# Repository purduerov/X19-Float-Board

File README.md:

# X19 Float Board

The Float Board manages buoyancy systems, motor drivers, sensor telemetry, and power distribution for the Purdue ROV X19 vehicle.

---

## 🚀 Quickstart: Opening the Project (Recommended)

**Always open the project using the 1-click launcher:**

* **Windows:** Double-click `LAUNCH_KICAD.bat`
* **macOS / Linux:** Run `./LAUNCH_KICAD.sh`

### What the Launcher Does Automatically:
1. ⚙️ **Configures Git Hooks & Clean Filters:** Sets up Git to strip volatile viewport/zoom coordinates on every commit, preventing merge conflicts.
2. 🔄 **Auto-Updates Component Library:** Pulls the freshest symbols, footprints, and 3D models from `purdue-rov-kicad-lib` before opening.
3. 📐 **Opens KiCad:** Launches `X19-Float-Board.kicad_pro` with all 6 central library categories pre-linked.

---

## Cloning the Repository
Clone recursively to ensure the central component library is initialized:
```bash
git clone --recursive https://github.com/purduerov/X19-Float-Board.git
cd X19-Float-Board
```

## Central Component Library & Manager GUI

The project links to the central `purdue-rov-kicad-lib` submodule mapped across 6 categories in `sym-lib-table` and `fp-lib-table`:
- `rov_passives`: Resistors, capacitors, inductors, crystals
- `rov_power`: Voltage regulators, buck/boost converters, MOSFETs, diodes
- `rov_logic`: MCUs, logic ICs, op-amps, drivers, level shifters
- `rov_connectors`: Power terminals, XT60, headers, USB, JST connectors
- `rov_sensors`: IMUs, temperature, pressure sensors
- `rov_mech`: Mounting holes, standoffs, test points

### Launching the Library Manager GUI
To browse parts, inspect footprints, edit properties, or add/delete components in the shared library:
- **Windows:** Double-click `libs\purdue-rov-kicad-lib\LIBRARY_MANAGER.bat`
- **macOS / Linux:** Run `./libs/purdue-rov-kicad-lib/LIBRARY_MANAGER.sh`

## Schematic Hierarchy

The schematic is organized across functional sub-sheets:
- `X19-Float-Board.kicad_sch`: Root top-level sheet.
- `pwr.kicad_sch`: Power regulation and distribution.
- `stm32.kicad_sch`: Main microcontroller circuit and programming interface.
- `Motor.kicad_sch`: Motor driver stages and control signals.
- `sensor.kicad_sch`: Environmental and diagnostic sensor telemetry.
- `rf.kicad_sch`: Wireless/radio transceiver circuitry.
- `switch.kicad_sch`: Power switching logic.

## Design Rules & Clearances

- High-voltage / high-current motor traces maintain isolation rules configured in `custom_rules.kicad_dru`.
- All symbols must adhere to central library guidelines.

## Automated CI/CD & DevOps Preflight Checks

All CI/CD automation and tooling are centralized in [`purduerov/pcb-devops`](https://github.com/purduerov/pcb-devops):
1. **Automated Git Clean Filters:** Configured automatically by `.githooks/pre-commit` to prevent viewport/zoom merge noise.
2. **KiCad Symbol Linting:** Validates mandatory fields (`MPN`, `Manufacturer`, `Category`, `DigiKey`, `Datasheet`, `Temp_Range`) on all library components.
3. **ERC & DRC Validation:** Executes Electrical and Design Rules Checks via KiBot in GitHub Actions.
4. **Artifact Generation:** Automatically exports Schematic PDFs, Board Layout PDFs, and Interactive HTML BOMs on every pull request.

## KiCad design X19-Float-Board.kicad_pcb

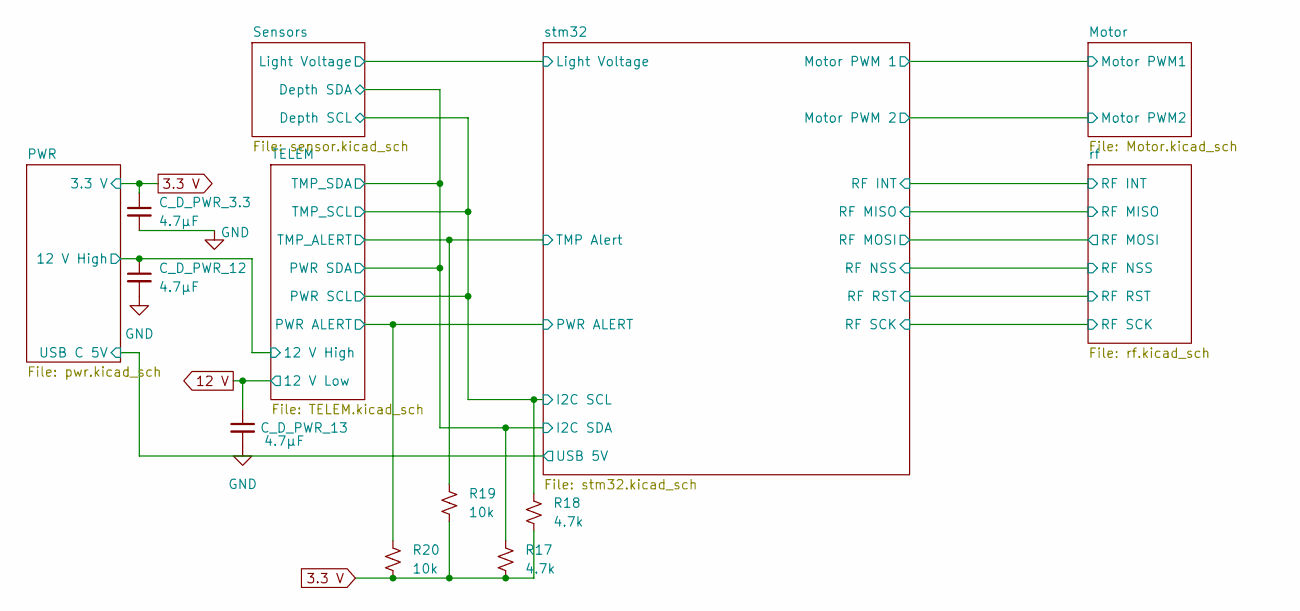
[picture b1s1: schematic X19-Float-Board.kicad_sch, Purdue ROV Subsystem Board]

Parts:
C_D_PWR_3.3, C_D_PWR_12, C_D_PWR_13: 4.7µF; C_0603_1608Metric
R17, R18: 4.7k; R_0603_1608Metric_Pad0.98x0.95mm_HandSolder
R19, R20: 10k; R_0603_1608Metric_Pad0.98x0.95mm_HandSolder

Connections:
3.3 V: C_D_PWR_3.3.1, R17.2, R18.2, R19.2, R20.2; also elsewhere on the board
12 V: C_D_PWR_13.1; also elsewhere on the board
/PWR/12 V High: C_D_PWR_12.1; also elsewhere on the board
/Sensors/Depth SCL: R18.1; also elsewhere on the board
/Sensors/Depth SDA: R17.1; also elsewhere on the board
/TELEM/PWR ALERT: R20.1; also elsewhere on the board
/TELEM/TMP_ALERT: R19.1; also elsewhere on the board
GND: C_D_PWR_3.3.2, C_D_PWR_12.2, C_D_PWR_13.2; also elsewhere on the board

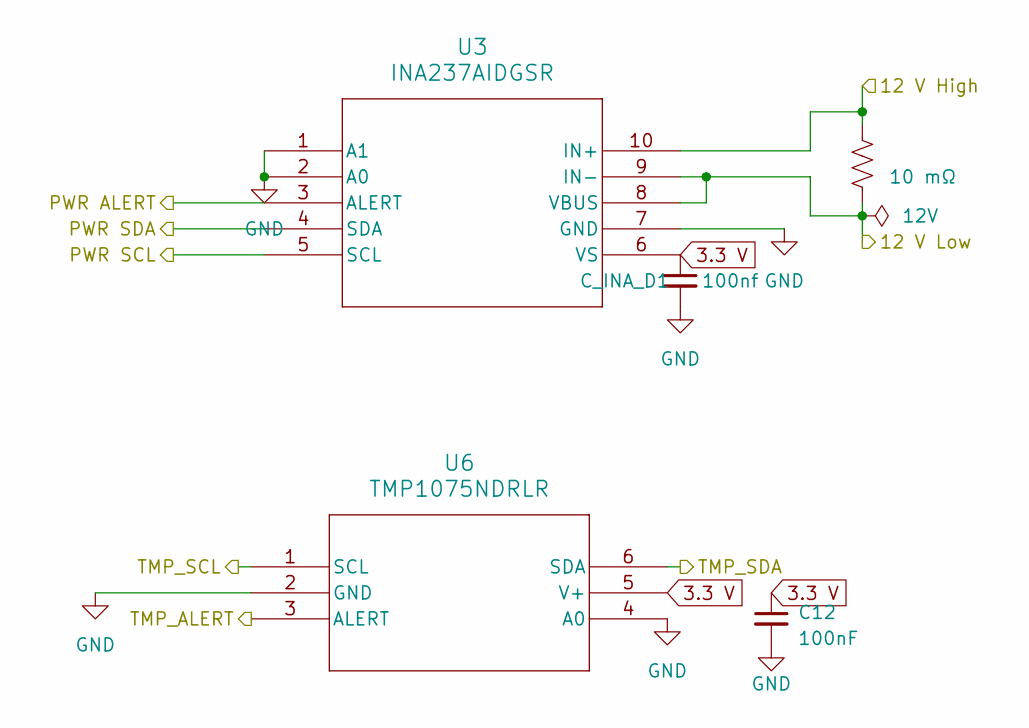
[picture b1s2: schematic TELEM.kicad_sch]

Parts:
C12: 100nF; C_0603_1608Metric_Pad1.08x0.95mm_HandSolder
C_INA_D1: 100nf; C_0603_1608Metric_Pad1.08x0.95mm_HandSolder
R1: 10 mΩ; R_2512_6332Metric_Pad1.40x3.35mm_HandSolder
U3: INA237AIDGSR; VSSOP_IDGSR_TEX; MPN INA237AIDGSR; DigiKey 296-INA237AIDGSRCT-ND
U6: TMP1075NDRLR; SOT5X3-6_DRL_TEX

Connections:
3.3 V: C12.1, C_INA_D1.1, U3.6 (VS), U6.5 (V+); also elsewhere on the board
12 V: R1.2, U3.8 (VBUS), U3.9 (IN-); also elsewhere on the board
/PWR/12 V High: R1.1, U3.10 (IN+); also elsewhere on the board
/Sensors/Depth SCL: U3.5 (SCL), U6.1 (SCL); also elsewhere on the board
/Sensors/Depth SDA: U3.4 (SDA), U6.6 (SDA); also elsewhere on the board
/TELEM/PWR ALERT: U3.3 (ALERT); also elsewhere on the board
/TELEM/TMP_ALERT: U6.3 (ALERT); also elsewhere on the board
GND: C12.2, C_INA_D1.2, U3.1 (A1), U3.2 (A0), U3.7 (GND), U6.2 (GND), U6.4 (A0); also elsewhere on the board

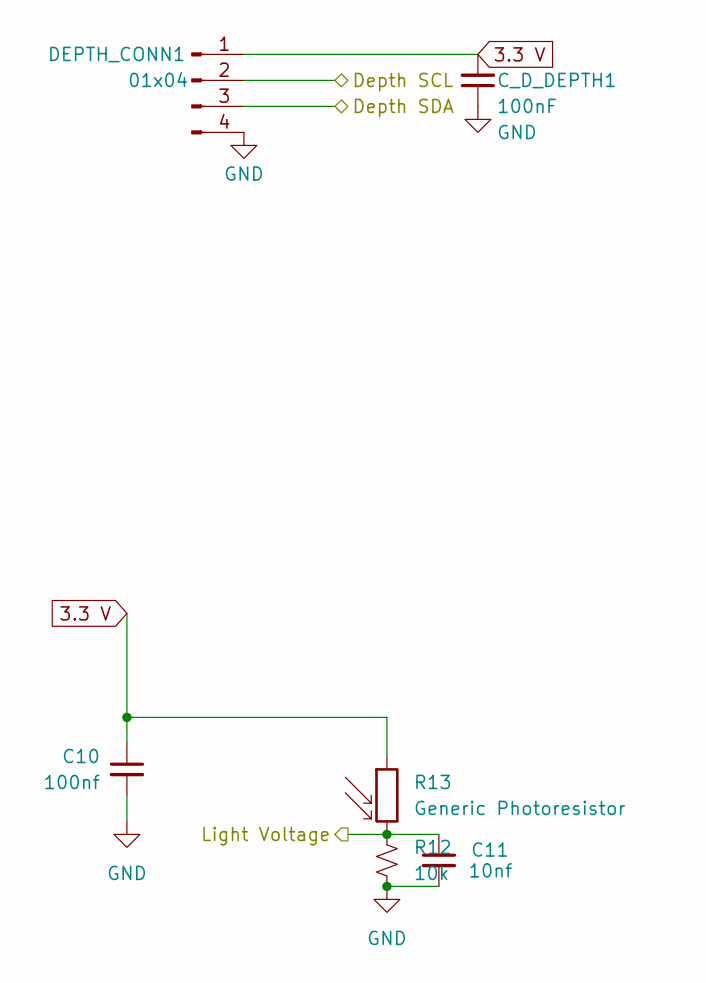
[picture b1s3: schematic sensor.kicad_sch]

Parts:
C10: 100nf; C_0603_1608Metric_Pad1.08x0.95mm_HandSolder
C11: 10nf; C_0603_1608Metric_Pad1.08x0.95mm_HandSolder
C_D_DEPTH1: 100nF; C_0603_1608Metric
DEPTH_CONN1: 01x04; Hirose_DF13-04P-1.25DS_1x04_P1.25mm_Horizontal
R12: 10k; R_0603_1608Metric_Pad0.98x0.95mm_HandSolder
R13: Generic Photoresistor; R_1206_3216Metric_Pad1.30x1.75mm_HandSolder

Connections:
3.3 V: C10.1, C_D_DEPTH1.2, DEPTH_CONN1.1, R13.1; also elsewhere on the board
/Sensors/Depth SCL: DEPTH_CONN1.2; also elsewhere on the board
/Sensors/Depth SDA: DEPTH_CONN1.3; also elsewhere on the board
/Sensors/Light Voltage: C11.1, R12.2, R13.2; also elsewhere on the board
GND: C10.2, C11.2, C_D_DEPTH1.1, DEPTH_CONN1.4, R12.1; also elsewhere on the board

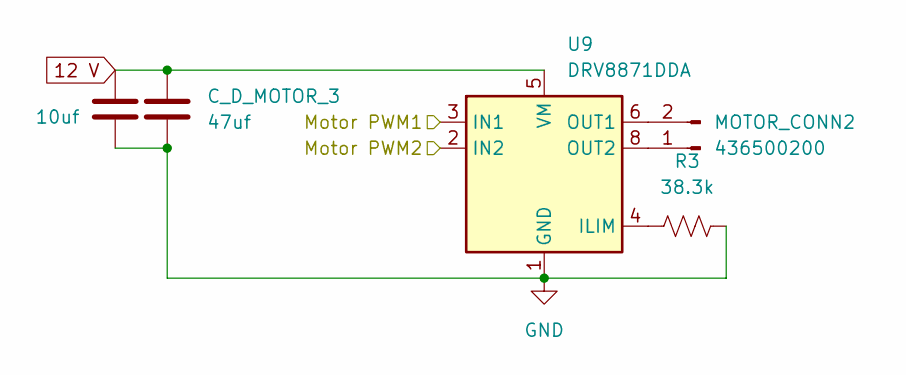
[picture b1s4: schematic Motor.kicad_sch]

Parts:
C_D_MOTOR_2: 10uf; C_0603_1608Metric_Pad1.08x0.95mm_HandSolder
C_D_MOTOR_3: 47uf; C_1206_3216Metric_Pad1.33x1.80mm_HandSolder
MOTOR_CONN2: 436500200; Molex_Micro-Fit_3.0_43650-0200_1x02_P3.00mm_Horizontal
R3: 38.3k; R_0603_1608Metric_Pad0.98x0.95mm_HandSolder
U9: DRV8871DDA; Texas_HTSOP-8-1EP_3.9x4.9mm_P1.27mm_EP2.95x4.9mm_Mask2.4x3.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

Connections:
12 V: C_D_MOTOR_2.2, C_D_MOTOR_3.1, U9.5 (VM); also elsewhere on the board
/Motor/Motor PWM1: U9.3 (IN1); also elsewhere on the board
/Motor/Motor PWM2: U9.2 (IN2); also elsewhere on the board
GND: C_D_MOTOR_2.1, C_D_MOTOR_3.2, R3.1, U9.1 (GND), U9.7 (GND), U9.9 (GND); also elsewhere on the board
unnamed: MOTOR_CONN2.1, U9.8 (OUT2)
unnamed: MOTOR_CONN2.2, U9.6 (OUT1)
unnamed: R3.2, U9.4 (ILIM)

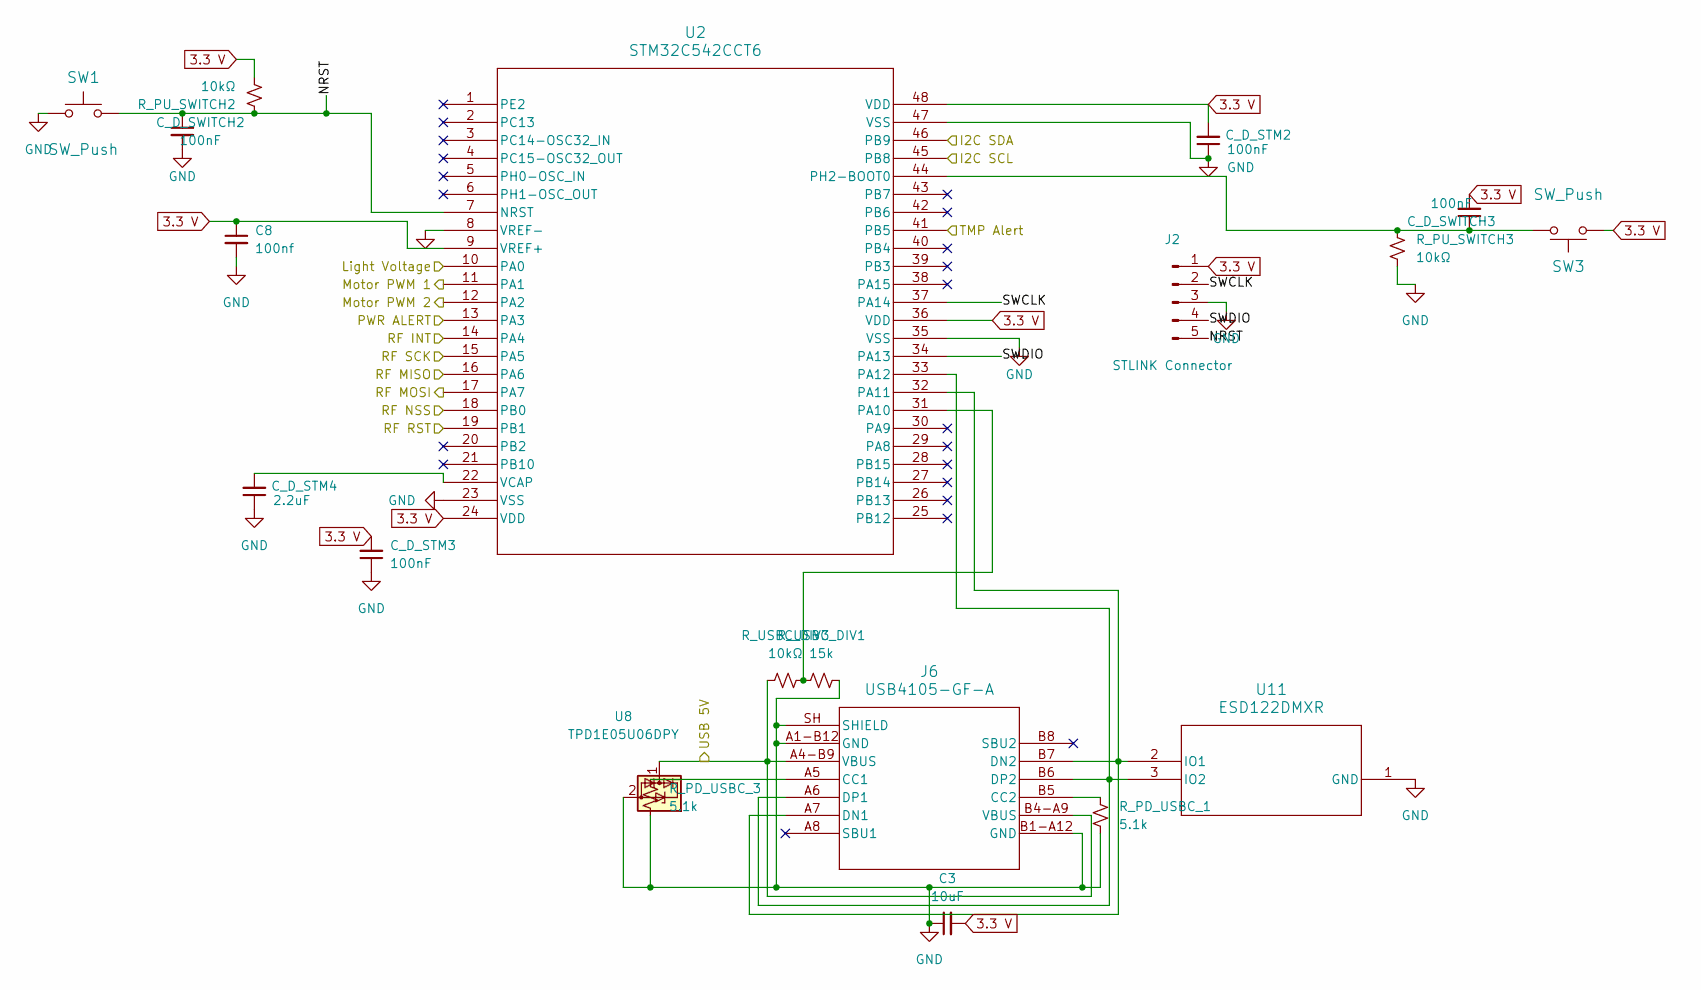
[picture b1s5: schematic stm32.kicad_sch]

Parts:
C3: 10uF; C_0805_2012Metric_Pad1.18x1.45mm_HandSolder
C8: 100nf; C_0603_1608Metric_Pad1.08x0.95mm_HandSolder
C_D_STM2, C_D_STM3: 100nF; C_0603_1608Metric
C_D_STM4: 2.2uF; C_0603_1608Metric
C_D_SWITCH2, C_D_SWITCH3: 100nF; C_0603_1608Metric
J2: STLINK Connector; PinHeader_1x05_P2.54mm_Vertical
J6: USB4105-GF-A; USB4105_GCT
R_PD_USBC_1, R_PD_USBC_3: 5.1k; R_0603_1608Metric
R_PU_SWITCH2, R_PU_SWITCH3: 10kΩ; R_0603_1608Metric
R_USBC_DIV1: 15k; R_0603_1608Metric
R_USBC_DIV3: 10kΩ; R_0603_1608Metric
SW1, SW3: SW_Push; SW_SPST_B3U-1000P
U2: STM32C542CCT6; LQFP48-7X7; MPN STM32C542CCT6
U8: TPD1E05U06DPY; Texas_DPY0002A_0.6x1mm_P0.65mm
U11: ESD122DMXR; DMX3_TEX

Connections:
3.3 V: C3.2, C8.1, C_D_STM2.2, C_D_STM3.2, C_D_SWITCH3.2, J2.1, R_PU_SWITCH2.1, SW3.1, U2.9 (VREF+), U2.24 (VDD), U2.36 (VDD), U2.48 (VDD); also elsewhere on the board
/Motor/Motor PWM1: U2.11 (PA1); also elsewhere on the board
/Motor/Motor PWM2: U2.12 (PA2); also elsewhere on the board
/PWR/USB C 5V: J6.A4-B9 (VBUS), J6.B4-A9 (VBUS), R_USBC_DIV3.1, U8.1 (I/O); also elsewhere on the board
/Sensors/Depth SCL: U2.45 (PB8); also elsewhere on the board
/Sensors/Depth SDA: U2.46 (PB9); also elsewhere on the board
/Sensors/Light Voltage: U2.10 (PA0); also elsewhere on the board
/TELEM/PWR ALERT: U2.13 (PA3); also elsewhere on the board
/TELEM/TMP_ALERT: U2.41 (PB5); also elsewhere on the board
/rf/RF INT: U2.14 (PA4); also elsewhere on the board
/rf/RF MISO: U2.16 (PA6); also elsewhere on the board
/rf/RF MOSI: U2.17 (PA7); also elsewhere on the board
/rf/RF NSS: U2.18 (PB0); also elsewhere on the board
/rf/RF RST: U2.19 (PB1); also elsewhere on the board
/rf/RF SCK: U2.15 (PA5); also elsewhere on the board
/stm32/NRST: C_D_SWITCH2.1, J2.5, R_PU_SWITCH2.2, SW1.2, U2.7 (NRST)
/stm32/SWCLK: J2.2, U2.37 (PA14)
/stm32/SWDIO: J2.4, U2.34 (PA13)
GND: C3.1, C8.2, C_D_STM2.1, C_D_STM3.1, C_D_STM4.1, C_D_SWITCH2.2, J2.3, J6.A1-B12 (GND), J6.B1-A12 (GND), J6.SH (SHIELD), R_PD_USBC_1.1, R_PD_USBC_3.1, R_PU_SWITCH3.1, R_USBC_DIV1.1, SW1.1, U2.8 (VREF-), U2.23 (VSS), U2.35 (VSS), U2.47 (VSS), U8.2 (GND), U11.1 (GND); also elsewhere on the board
unnamed: J6.A5 (CC1), R_PD_USBC_3.2
unnamed: J6.B5 (CC2), R_PD_USBC_1.2
unnamed: J6.A7 (DN1), J6.B7 (DN2), U2.32 (PA11), U11.2 (IO1)
unnamed: J6.A6 (DP1), J6.B6 (DP2), U2.33 (PA12), U11.3 (IO2)
unnamed: R_USBC_DIV1.2, R_USBC_DIV3.2, U2.31 (PA10)
unnamed: C_D_SWITCH3.1, R_PU_SWITCH3.2, SW3.2, U2.44 (PH2-BOOT0)
unnamed: C_D_STM4.2, U2.22 (VCAP)

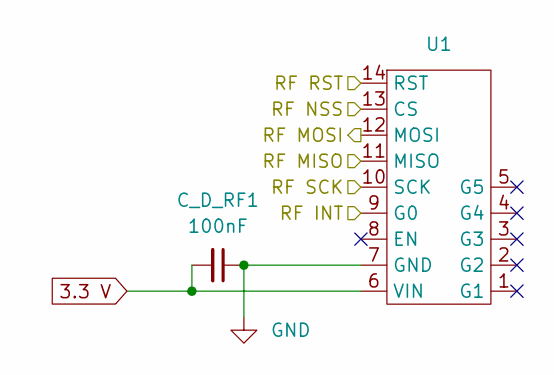
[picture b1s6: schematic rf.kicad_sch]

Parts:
C_D_RF1: 100nF; C_0603_1608Metric
U1: rf module

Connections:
3.3 V: C_D_RF1.2, U1.6 (VIN); also elsewhere on the board
/rf/RF INT: U1.9 (G0); also elsewhere on the board
/rf/RF MISO: U1.11 (MISO); also elsewhere on the board
/rf/RF MOSI: U1.12 (MOSI); also elsewhere on the board
/rf/RF NSS: U1.13 (CS); also elsewhere on the board
/rf/RF RST: U1.14 (RST); also elsewhere on the board
/rf/RF SCK: U1.10 (SCK); also elsewhere on the board
GND: C_D_RF1.1, U1.7 (GND); also elsewhere on the board

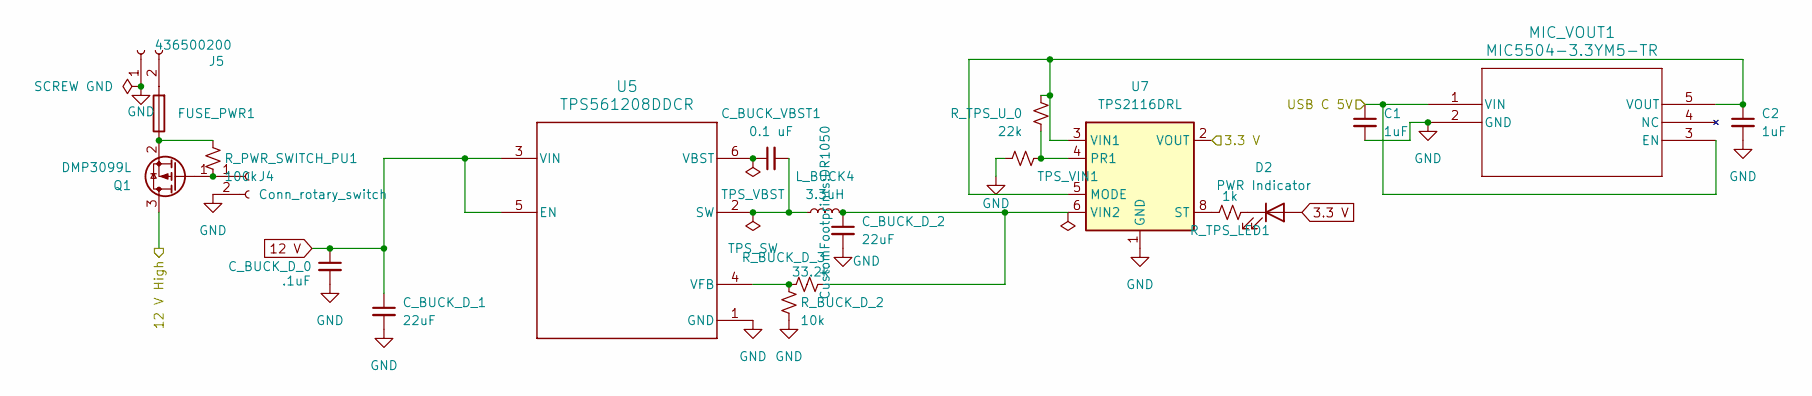
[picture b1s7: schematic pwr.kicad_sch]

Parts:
C1, C2: 1uF; C_0603_1608Metric_Pad1.08x0.95mm_HandSolder
C_BUCK_D_0: .1uF; C_0603_1608Metric_Pad1.08x0.95mm_HandSolder
C_BUCK_D_1, C_BUCK_D_2: 22uF; C_1210_3225Metric_Pad1.33x2.70mm_HandSolder
C_BUCK_VBST1: 0.1 uF; C_0603_1608Metric_Pad1.08x0.95mm_HandSolder
D2: PWR Indicator; LED_0805_2012Metric_Pad1.15x1.40mm_HandSolder
FUSE_PWR1: 2A 24V PTC fuse; Fuse_1812_4532Metric
J4: Conn_rotary_switch; JST_PH_B2B-PH-K_1x02_P2.00mm_Vertical
J5: 436500200; Molex_Micro-Fit_3.0_43650-0200_1x02_P3.00mm_Horizontal
L_BUCK4: 3.3uH; DR1050
MIC_VOUT1: MIC5504-3.3YM5-TR; SOT-23-5_MC_MCH; MPN MIC5504-3.3YM5-TR; DigiKey 576-4763-1-ND
Q1: DMP3099L; SOT-23
R_BUCK_D_2: 10k; R_0603_1608Metric_Pad0.98x0.95mm_HandSolder
R_BUCK_D_3: 33.2k; R_0603_1608Metric_Pad0.98x0.95mm_HandSolder
R_PWR_SWITCH_PU1: 100k; R_0603_1608Metric_Pad0.98x0.95mm_HandSolder
R_TPS_D_0: 15k; R_0603_1608Metric_Pad0.98x0.95mm_HandSolder
R_TPS_LED1: 1k; R_0603_1608Metric_Pad0.98x0.95mm_HandSolder
R_TPS_U_0: 22k; R_0603_1608Metric_Pad0.98x0.95mm_HandSolder
U5: TPS561208DDCR; DDC0006A_N
U7: TPS2116DRL; SOT-583-8

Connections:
3.3 V: D2.2 (A), U7.2 (VOUT), U7.7 (VOUT); also elsewhere on the board
12 V: C_BUCK_D_0.1, C_BUCK_D_1.1, U5.3 (VIN), U5.5 (EN); also elsewhere on the board
/PWR/12 V High: Q1.3 (D); also elsewhere on the board
/PWR/USB C 5V: C1.1, MIC_VOUT1.1 (VIN), MIC_VOUT1.3 (EN); also elsewhere on the board
GND: C1.2, C2.2, C_BUCK_D_0.2, C_BUCK_D_1.2, C_BUCK_D_2.2, J4.2, J5.1, MIC_VOUT1.2 (GND), R_BUCK_D_2.2, R_TPS_D_0.1, U5.1 (GND), U7.1 (GND); also elsewhere on the board
unnamed: D2.1 (K), R_TPS_LED1.2
unnamed: J4.1, Q1.1 (G), R_PWR_SWITCH_PU1.2
unnamed: FUSE_PWR1.2, J5.2
unnamed: C2.1, MIC_VOUT1.5 (VOUT), R_TPS_U_0.1, U7.3 (VIN1), U7.5 (MODE)
unnamed: FUSE_PWR1.1, Q1.2 (S), R_PWR_SWITCH_PU1.1
unnamed: C_BUCK_VBST1.2, L_BUCK4.1, U5.2 (SW)
unnamed: C_BUCK_VBST1.1, U5.6 (VBST)
unnamed: R_BUCK_D_2.1, R_BUCK_D_3.1, U5.4 (VFB)
unnamed: R_TPS_D_0.2, R_TPS_U_0.2, U7.4 (PR1)
unnamed: R_TPS_LED1.1, U7.8 (ST)
unnamed: C_BUCK_D_2.1, L_BUCK4.2, R_BUCK_D_3.2, U7.6 (VIN2)

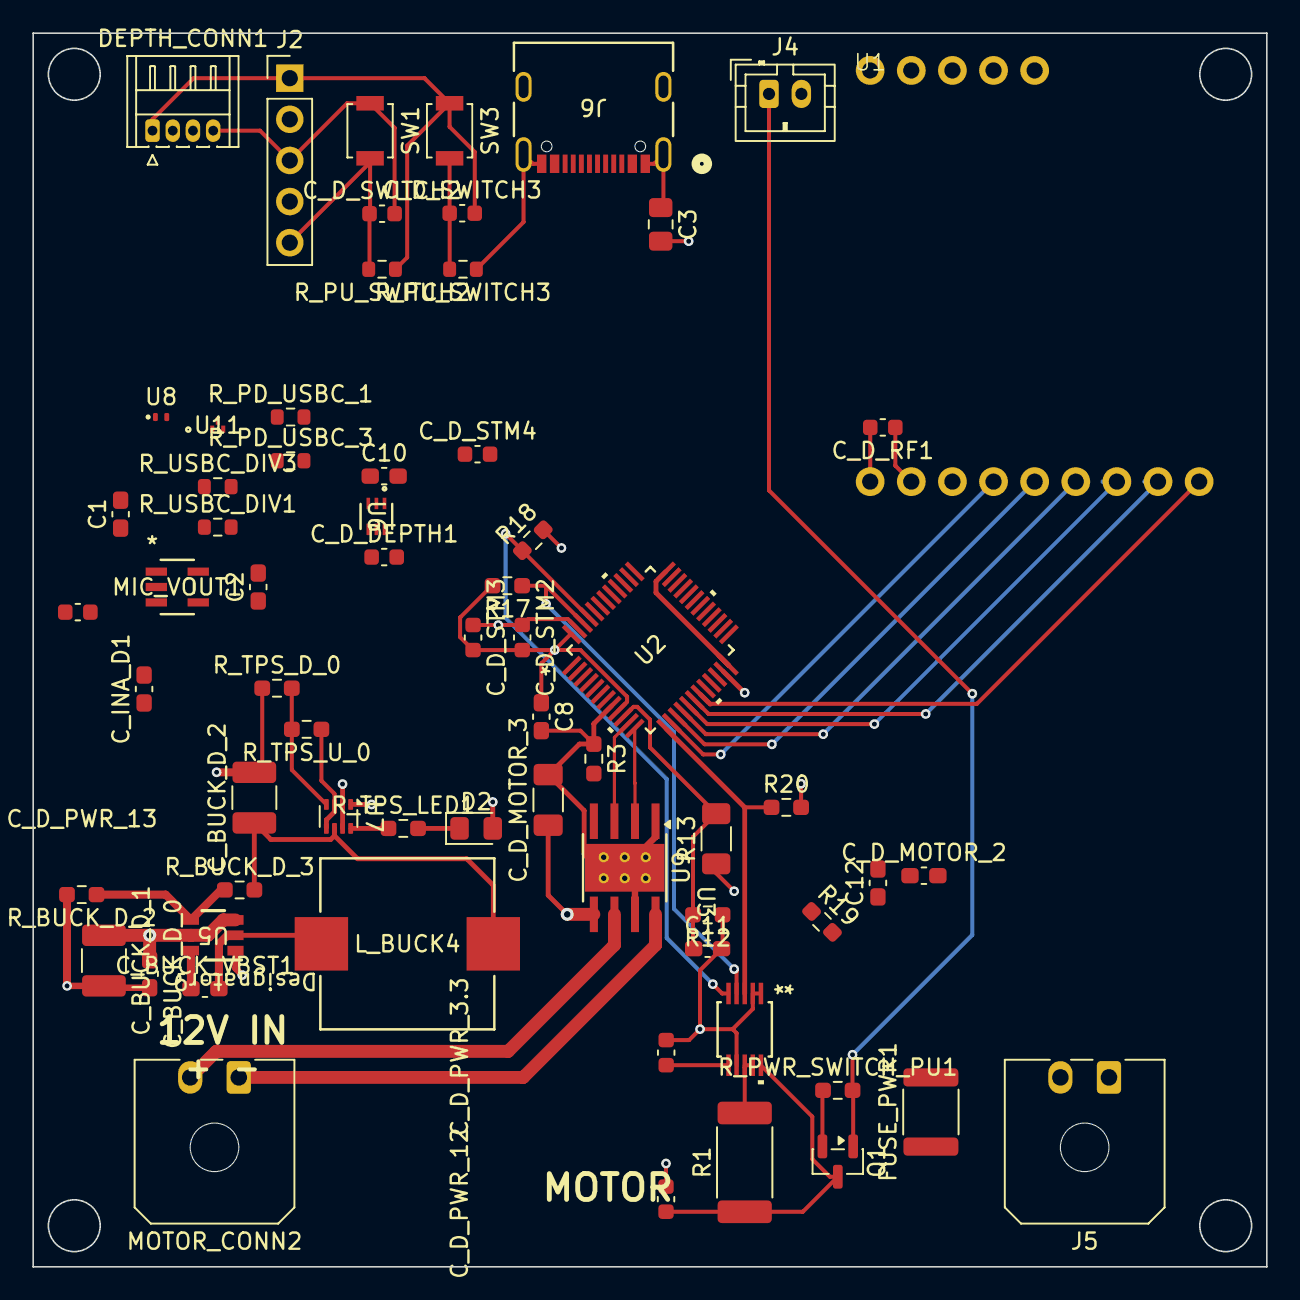
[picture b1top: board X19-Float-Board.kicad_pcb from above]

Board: 4 copper layers, 76.2 x 76.2 mm, 66 parts (0 on the bottom side), 42 nets.

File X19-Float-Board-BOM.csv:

Row,Description,Part,References,Value,Footprint,Quantity Per PCB,Status,Datasheet,Manufacturer,MPN,DigiKey,Temp_Range,Category,Verified,Sim.Pins
1,"Unpolarized capacitor, small symbol",C_Small,C11,10nf,C_0603_1608Metric_Pad1.08x0.95mm_HandSolder,1, ,,,,,,,,
2,"Unpolarized capacitor, small symbol",C_Small,C8 C10 C12 C_INA_D1,100nf,C_0603_1608Metric_Pad1.08x0.95mm_HandSolder,4, ,,,,,,,,
3,"Unpolarized capacitor, small symbol",C_Small,C1 C2,1uF,C_0603_1608Metric_Pad1.08x0.95mm_HandSolder,2, ,,,,,,,,
4,"Unpolarized capacitor, small symbol",C_Small,C3,10uF,C_0805_2012Metric_Pad1.18x1.45mm_HandSolder,1, ,,,,,,,,
5,"Unpolarized capacitor, small symbol",C_Small,C_BUCK_D_0,.1uF,C_0603_1608Metric_Pad1.08x0.95mm_HandSolder,1, ,,,,,,,,
6,"Unpolarized capacitor, small symbol",C_Small,C_BUCK_D_1 C_BUCK_D_2,22uF,C_1210_3225Metric_Pad1.33x2.70mm_HandSolder,2, ,,,,,,,,
7,"Unpolarized capacitor, small symbol",C_Small,C_BUCK_VBST1,0.1 uF,C_0603_1608Metric_Pad1.08x0.95mm_HandSolder,1, ,,,,,,,,
8,"Unpolarized capacitor, small symbol",C_Small,C_D_DEPTH1 C_D_RF1 C_D_STM2 C_D_STM3 C_D_SWITCH2 C_D_SWITCH3,100nF,C_0603_1608Metric,6, ,,,,,,,,
9,Unpolarized capacitor,C,C_D_MOTOR_2,10uf,C_0603_1608Metric_Pad1.08x0.95mm_HandSolder,1, ,,,,,,,,
10,Unpolarized capacitor,C,C_D_MOTOR_3,47uf,C_1206_3216Metric_Pad1.33x1.80mm_HandSolder,1, ,,,,,,,,
11,"Unpolarized capacitor, small symbol",C_Small,C_D_PWR_3.3 C_D_PWR_12 C_D_PWR_13,4.7µF,C_0603_1608Metric,3, ,,,,,,,,
12,"Unpolarized capacitor, small symbol",C_Small,C_D_STM4,2.2uF,C_0603_1608Metric,1, ,,,,,,,,
13,"Unpolarized capacitor, small symbol",100nF,C_D_SWITCH1,100nF,C_0603_1608Metric,1, ,,,,,,,,
14,Light emitting diode,LED,D2,PWR Indicator,LED_0805_2012Metric_Pad1.15x1.40mm_HandSolder,1, ,,,,,,,,1=K 2=A
15,"Generic connector, single row, 01x04, script generated",Conn_01x04_Pin,DEPTH_CONN1,01x04,Hirose_DF13-04P-1.25DS_1x04_P1.25mm_Horizontal,1, ,,,,,,,,
16,Fuse,Fuse,FUSE_PWR1,2A 24V PTC fuse,Fuse_1812_4532Metric,1, ,,,,,,,,
17,Molex Micro-Fit 3.0 2-pin right-angle PCB header (12V battery input),Conn_01x02_Socket,J5,436500200,Molex_Micro-Fit_3.0_43650-0200_1x02_P3.00mm_Horizontal,1, ,https://www.molex.com/en-us/products/part-detail-pdf/4365002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,,,,,,,
18,"Generic connector, single row, 01x02, script generated",Conn_01x02_Socket,J4,Conn_rotary_switch,JST_PH_B2B-PH-K_1x02_P2.00mm_Vertical,1, ,,,,,,,,
19,"Generic connector, single row, 01x05, script generated",Conn_01x05_Pin,J2,STLINK Connector,PinHeader_1x05_P2.54mm_Vertical,1, ,,,,,,,,
20,,USB4105-GF-A,J6,USB4105-GF-A,USB4105_GCT,1, ,USB4105-GF-A,,,,,,,
21,"Inductor, small symbol",L_Small,L_BUCK4,3.3uH,DR1050,1, ,,,,,,,,
22,300mA Single LDO Regulator 3.3V Output SOT-23-5,MIC5504-3.3YM5-TR,MIC_VOUT1,MIC5504-3.3YM5-TR,SOT-23-5_MC_MCH,1, ,https://ww1.microchip.com/downloads/en/DeviceDoc/MIC550X-300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,Microchip Technology,MIC5504-3.3YM5-TR,576-4763-1-ND,-40°C to 125°C,Power,Yes,
23,Molex Micro-Fit 3.0 2-pin right-angle PCB header (pump motor),Conn_01x02_Pin,MOTOR_CONN2,436500200,Molex_Micro-Fit_3.0_43650-0200_1x02_P3.00mm_Horizontal,1, ,https://www.molex.com/en-us/products/part-detail-pdf/4365002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,,,,,,,
24,"-3.8A Id, -30V Vds, P-Channel MOSFET, SOT-23",DMP3099L,Q1,DMP3099L,SOT-23,1, ,https://www.diodes.com/assets/Datasheets/DMP3099L.pdf,,,,,,,
25,"Resistor, US symbol",R_US,R1,10 mΩ,R_2512_6332Metric_Pad1.40x3.35mm_HandSolder,1, ,,,,,,,,
26,"Resistor, small US symbol",R_Small_US,R17 R18,4.7k,R_0603_1608Metric_Pad0.98x0.95mm_HandSolder,2, ,,,,,,,,
27,"Resistor, small US symbol",R_Small_US,R12 R19 R20 R_BUCK_D_2,10k,R_0603_1608Metric_Pad0.98x0.95mm_HandSolder,4, ,,,,,,,,
28,"Resistor, US symbol",R_US,R3,38.3k,R_0603_1608Metric_Pad0.98x0.95mm_HandSolder,1, ,,,,,,,,
29,Photoresistor,R_Photo,R13,Generic Photoresistor,R_1206_3216Metric_Pad1.30x1.75mm_HandSolder,1, ,,,,,,,,
30,"Resistor, small US symbol",R_Small_US,R_BUCK_D_3,33.2k,R_0603_1608Metric_Pad0.98x0.95mm_HandSolder,1, ,,,,,,,,
31,"Resistor, small US symbol",R_Small_US,R_PD_USBC_1 R_PD_USBC_3,5.1k,R_0603_1608Metric,2, ,,,,,,,,
32,"Resistor, small US symbol",R_Small_US,R_PU_SWITCH2 R_PU_SWITCH3 R_USBC_DIV3,10kΩ,R_0603_1608Metric,3, ,,,,,,,,
33,"Resistor, small US symbol",R_Small_US,R_PWR_SWITCH_PU1,100k,R_0603_1608Metric_Pad0.98x0.95mm_HandSolder,1, ,,,,,,,,
34,"Resistor, small US symbol",R_Small_US,R_TPS_D_0,15k,R_0603_1608Metric_Pad0.98x0.95mm_HandSolder,1, ,,,,,,,,
35,"Resistor, small US symbol",R_Small_US,R_TPS_LED1,1k,R_0603_1608Metric_Pad0.98x0.95mm_HandSolder,1, ,,,,,,,,
36,"Resistor, small US symbol",R_Small_US,R_TPS_U_0,22k,R_0603_1608Metric_Pad0.98x0.95mm_HandSolder,1, ,,,,,,,,
37,"Resistor, small US symbol",R_Small_US,R_USBC_DIV1,15k,R_0603_1608Metric,1, ,,,,,,,,
38,"Push button switch, generic, two pins",SW_Push,SW1 SW3,SW_Push,SW_SPST_B3U-1000P,2, ,,,,,,,,
39,"Brushed DC Motor Driver, PWM Control, 45V, 3.6A, Current limiting, HTSOP-8",DRV8871DDA,U9,DRV8871DDA,Texas_HTSOP-8-1EP_3.9x4.9mm_P1.27mm_EP2.95x4.9mm_Mask2.4x3.1mm_ThermalVias,1, ,http://www.ti.com/lit/ds/symlink/drv8871.pdf,,,,,,,
40,,ESD122DMXR,U11,ESD122DMXR,DMX3_TEX,1, ,https://www.ti.com/lit/gpn/esd122,,,,,,,
41,"85V, 16-Bit, High-Precision Current/Voltage/Power Monitor with I2C",INA237AIDGSR,U3,INA237AIDGSR,VSSOP_IDGSR_TEX,1, ,https://www.ti.com/lit/ds/symlink/ina237.pdf,Texas Instruments,INA237AIDGSR,296-INA237AIDGSRCT-ND,-40°C to 125°C,Sensors,Yes,
42,"ARM Cortex-M33 32-bit MCU+FPU, 144MHz, 256KB Flash, 64KB RAM, LQFP-48",STM32C542CCT6,U2,STM32C542CCT6,LQFP48-7X7,1, ,https://www.st.com/resource/en/datasheet/stm32c542cc.pdf,STMicroelectronics,STM32C542CCT6,https://www.digikey.com/en/products/detail/stmicroelectronic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,-40°C to 125°C,Logic,,
43,,TMP1075NDRLR,U6,TMP1075NDRLR,SOT5X3-6_DRL_TEX,1, ,https://www.ti.com/lit/gpn/tmp1075,,,,,,,
44,"1-Channel ESD Protection for Super-Speed USB 3.0 Interface, X1SON-2",TPD1E05U06DPY,U8,TPD1E05U06DPY,Texas_DPY0002A_0.6x1mm_P0.65mm,1, ,https://www.ti.com/lit/ds/symlink/tpd1e05u06.pdf,,,,,,,
45,"2 Channnels Power Mux with Manual and Priority Switchover, 1.6-5.5V Input Voltage, 2.5A Output Current, Ron 40 mOhm, SOT-583-8",TPS2116DRL,U7,TPS2116DRL,SOT-583-8,1, ,https://www.ti.com/lit/ds/symlink/tps2116.pdf,,,,,,,
46,,TPS561208DDCR,U5,TPS561208DDCR,DDC0006A_N,1, ,https://www.ti.com/lit/gpn/tps561208,,,,,,,
47,,rfm95adafruitmodule,U1,~,rf module,1, ,,,,,,,,





Project info:
Schematic:,X19-Float-Board
Variant:,default
Revision:,
Date:,2026-11-23_23-12-14
KiCad Version:,10.0.5-unknown-202607221313~667fa36054~ubuntu25.10.1
Statistics:
Component Groups:,47
Component Count:,67
Fitted Components:,67
Number of PCBs:,1
Total Components:,67

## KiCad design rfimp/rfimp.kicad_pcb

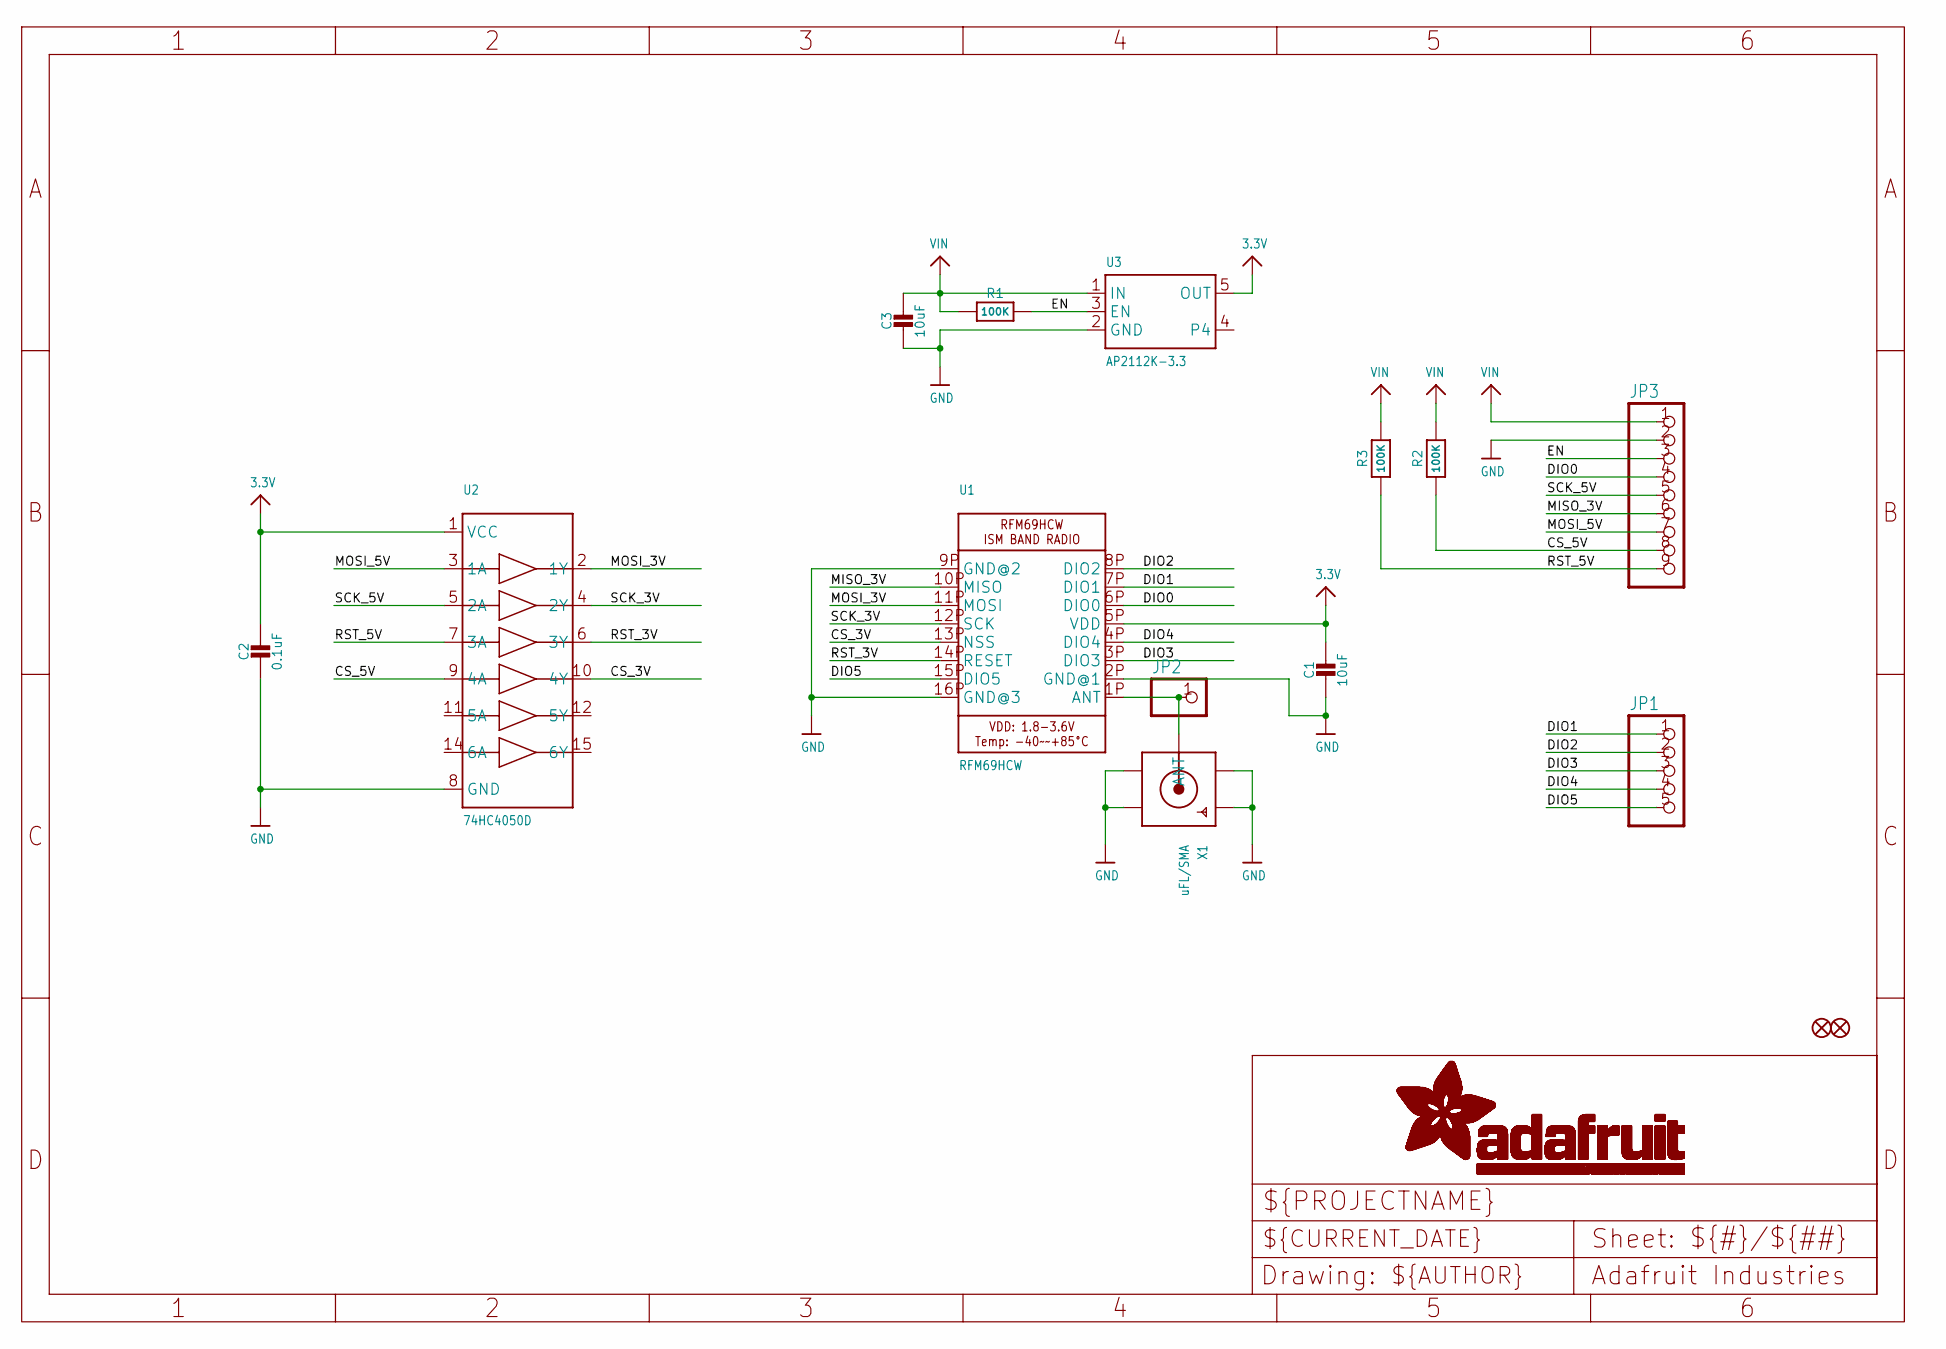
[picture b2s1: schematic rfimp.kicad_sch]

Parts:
C1, C3: 10uF; 0805-NO
C2: 0.1uF; 0805-NO
FID1, FID2: FIDUCIAL""; FIDUCIAL_1MM
JP1: HEADER-1X570MIL; 1X05_ROUND_70
JP2: HEADER-1X1ROUND; 1X01_ROUND
JP3: HEADER-1X970MIL; 1X09_ROUND_70
R1, R2, R3: 100K; 0805-NO
U1: RFM69HCW; RFMHCW_SMT
U2: 74HC4050D; TSSOP16
U3: AP2112K-3.3; SOT23-5
X1: uFL/SMA; SMA_EDGELAUNCH_UFL

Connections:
3.3V: C1.1, C2.1, U1.5P (VDD), U2.1 (VCC), U3.5 (OUT)
CS_3V: U1.13P (NSS), U2.10 (4Y)
CS_5V: JP3.8, R2.1, U2.9 (4A)
DIO0: JP3.4, U1.6P (DIO0)
DIO1: JP1.1, U1.7P (DIO1)
DIO2: JP1.2, U1.8P (DIO2)
DIO3: JP1.3, U1.3P (DIO3)
DIO4: JP1.4, U1.4P (DIO4)
DIO5: JP1.5, U1.15P (DIO5)
EN: JP3.3, R1.2, U3.3 (EN)
GND: C1.2, C2.2, C3.2, JP3.2, U1.2P (GND@1), U1.9P (GND@2), U1.16P (GND@3), U2.8 (GND), U3.2 (GND), X1.GND@1 (GND1), X1.GND@2 (GND2), X1.GND@3 (GND3), X1.GND@4 (GND4)
MISO_3V: JP3.6, U1.10P (MISO)
MOSI_3V: U1.11P (MOSI), U2.2 (1Y)
MOSI_5V: JP3.7, U2.3 (1A)
unnamed: JP2.1, U1.1P (ANT), X1.P (ANT)
RST_3V: U1.14P (RESET), U2.6 (3Y)
RST_5V: JP3.9, R3.1, U2.7 (3A)
SCK_3V: U1.12P (SCK), U2.4 (2Y)
SCK_5V: JP3.5, U2.5 (2A)
VIN: C3.1, JP3.1, R1.1, R2.2, R3.2, U3.1 (IN)

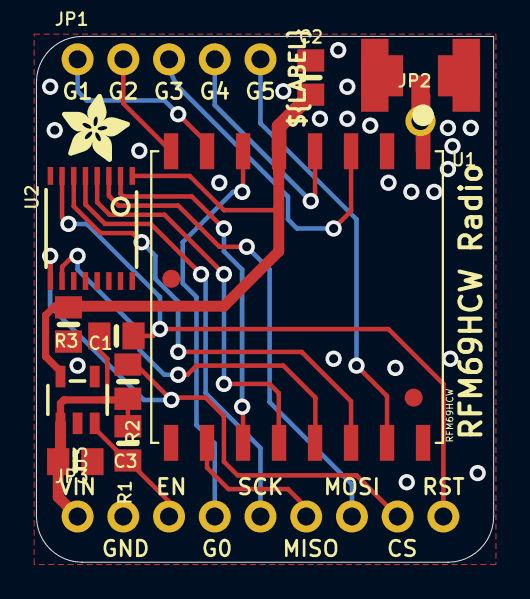
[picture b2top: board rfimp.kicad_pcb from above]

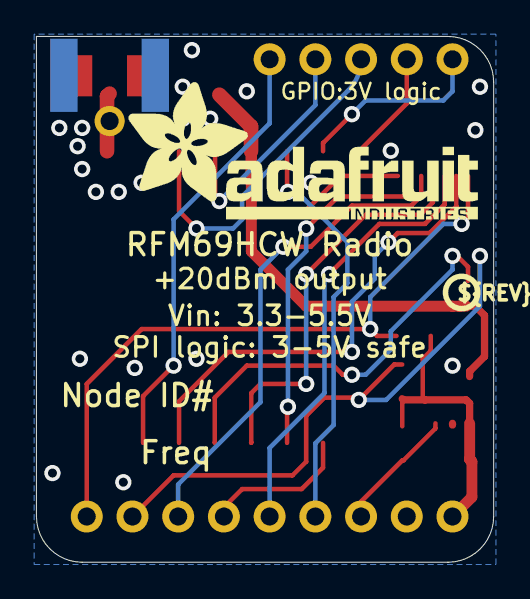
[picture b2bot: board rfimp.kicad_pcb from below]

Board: 2 copper layers, 25.4 x 29.2 mm, 18 parts (2 on the bottom side), 20 nets.

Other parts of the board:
U$8: ADAFRUIT_3.5MM
U$14: PCBFEAT-REV-040
U$19: ADAFRUIT_TEXT_20MM
